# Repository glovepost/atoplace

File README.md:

<p align="center">
  
</p>

---

<p align="center">
  <strong>The AI Pair Designer for Professional PCB Layout</strong>
</p>

**atoplace** is an intelligent orchestration layer for PCB design that bridges the gap between schematic and physical layout. It automates the tedious 80% of design—placement optimization and DFM validation—while strictly adhering to "Manhattan" aesthetics and Signal Integrity (SI) best practices.

Designed to work seamlessly with **[atopile](https://atopile.io)** and **[KiCad](https://kicad.org)**.

## 🚀 Why atoplace?

PCB layout automation has historically been "black box" and "messy"—producing organic, unreadable layouts that professional engineers reject. atoplace takes a different approach:

*   **Human-Grade Aesthetics**: We don't just minimize wirelength. We enforce **grids**, **alignment**, and **orthogonal routing** so the result looks like *you* designed it.
*   **Physics-First**: We model high-degree nets (GND/VCC) correctly to prevent component collapse, and prioritize critical signals (USB, RF) before general routing.
*   **Transparent & Interactive**: No lock-in. The source of truth is always your `.kicad_pcb` file. You can take over manually at any second.

## ✨ Key Features

- **🧩 Manhattan Legalizer**: Transforms "organic" force-directed placements into professional, grid-snapped, and row-aligned layouts using PCA axis detection and Abacus-style overlap resolution.
- **🧠 Intelligent Placement**: Force-directed annealing engine with a **Star Model** for stable high-degree net (GND/VCC) handling and adaptive damping for oscillation control.
- **🚀 A* Routing**: High-performance, deterministic geometric router using a **Greedy Multiplier** ($w=2-3$) and **Spatial Hash Indexing** for O(~1) collision detection.
- **🔍 Confidence Scoring**: Automated assessment of your board's routability, signal integrity risks, and DFM compliance.
- **💬 Natural Language Control**: "Move the USB connector to the left edge", "Align these capacitors", "Keep the crystal near the MCU".
- **🔌 Atopile Native**: First-class support for `atopile` projects with `ato-lock.yaml` parsing, module-aware grouping, and **`atoplace.lock` sidecar persistence** to preserve placements across rebuilds.
- **📊 Interactive Visualization**: Unified SVG delta viewer with real-time playback, layer toggles, grid customization, force vector display, routing trace visualization, and A* debug mode for step-by-step algorithm analysis.

## 🛠️ Installation

```bash
pip install atoplace
```

### Requirements
- **Python 3.10+**
- **KiCad 8.0+** (atoplace uses the `pcbnew` Python API)

> **Pro Tip:** atoplace works best when run using the Python interpreter bundled with KiCad:

**macOS:**
```bash
/Applications/KiCad/KiCad.app/Contents/Frameworks/Python.framework/Versions/Current/bin/python3 -m pip install atoplace
```

**Windows:**
```powershell
"C:\Program Files\KiCad\8.0\bin\python.exe" -m pip install atoplace
```

## ⚡ Quick Start

### 1. Optimize Placement
Automatically place components with "Manhattan" legalization:
```bash
atoplace place board.kicad_pcb --grid 0.5 --constraints "USB on left edge"
```

### 2. Route the Board
Route all nets using the internal A* geometric planner:
```bash
atoplace route board.kicad_pcb --visualize
```

### 3. Validate Layout
Check your board against DFM rules (JLCPCB, OSH Park, etc.):
```bash
atoplace validate board.kicad_pcb --dfm jlcpcb_standard
```

### 4. Interactive Mode
Refine your design using natural language:
```bash
atoplace interactive board.kicad_pcb
# > "Rotate U1 45 degrees"
# > "Move C1 closer to U1"
# > "Save"
```

### 5. MCP Server (LLM Integration)
Expose atoplace tools to AI agents via the Model Context Protocol:
```bash
atoplace mcp --launch
```

See [MCP Server](#-mcp-server) section below for details.

## 🗺️ Roadmap

- **Milestone A (Q1 2026): Solid Foundation** ✅
  - [x] Manhattan Legalizer (Grid snapping & PCA Alignment).
  - [x] Physics Engine scaling (Star Model & Adaptive Damping).
  - [x] Atopile `ato-lock.yaml` and module hierarchy integration.
- **Milestone B (Q1-Q2 2026): Routing & Persistence** ✅
  - [x] **A* Geometric Planner** (Greedy Multiplier & Spatial Indexing).
  - [x] **MCP Server** with 40+ tools for LLM agent integration.
  - [x] **Live KiCad IPC** via kipy for real-time component manipulation (KiCad 9+).
  - [x] **`atoplace.lock` Sidecar Persistence** for atopile projects.
  - [x] **Unified Visualization** (SVG delta viewer with routing support).
  - [x] **BGA/QFN Fanout Generator** (dogbone & via-in-pad strategies).
  - [x] **Pin Swap Optimization** (bipartite matching for crossing reduction).
- **Milestone C (Q2 2026): Professional Agent** 🚧
  - [x] Differential Pair Detection (auto-detect from net names).
  - [ ] Differential Pair Coupled Routing.
  - [ ] Deep Signal Integrity Analysis (Crosstalk/Impedance).
  - [ ] Automated Manufacturing Outputs (Gerbers/BOM/PNP).
  - [ ] Multi-board design support.

## 📂 Architecture

```
atoplace/
├── board/          # Board abstraction & KiCad/Atopile adapters
│   ├── abstraction.py      # Board, Component, Net, Pad data models
│   ├── kicad_adapter.py    # KiCad pcbnew integration
│   ├── lock_file.py        # atoplace.lock sidecar persistence
│   └── atopile_adapter.py  # Atopile project loader
├── placement/      # Force-directed physics & Manhattan Legalizer
│   ├── force_directed.py   # Physics Engine (Star Model, adaptive damping)
│   ├── legalizer.py        # Manhattan Pipeline with PCA alignment
│   ├── module_detector.py  # Functional module hierarchy analysis
│   ├── constraints.py      # Placement constraints (Proximity, Edge, Zone, etc.)
│   └── visualizer.py       # SVG delta visualization with frame capture
├── routing/        # A* Geometric Router
│   ├── astar_router.py     # Core A* with Greedy Multiplier (w=2-3)
│   ├── manager.py          # Multi-phase routing pipeline
│   ├── spatial_index.py    # O(~1) collision detection via spatial hashing
│   ├── obstacle_map.py     # Obstacle generation from board
│   ├── diff_pairs.py       # Differential pair detection
│   ├── visualizer.py       # Routing visualization with A* debug
│   └── fanout/             # BGA/QFN escape routing
├── visualization/  # Unified visualization system
│   └── assets/             # External JS/CSS for HTML viewer
│       ├── svg-delta-viewer.js  # Interactive SVG playback engine
│       └── styles.css      # KiCad-inspired dark theme
├── nlp/            # Natural Language & Intent Engine
│   └── constraint_parser.py  # Parse "USB on left edge" to constraints
├── validation/     # Confidence Scorer & DFM/DRC Checker
│   ├── confidence.py       # Design quality assessment
│   └── drc.py              # Design rule checking
├── mcp/            # MCP Server for LLM Integration
│   ├── server.py           # FastMCP server with 40+ tools
│   ├── backends.py         # Backend mode detection & factory
│   ├── kipy_session.py     # Live KiCad IPC session (KiCad 9+)
│   └── context/            # Context generators (semantic grid, module map)
└── cli.py          # CLI entry point
```

## 🤖 MCP Server

atoplace includes a **Model Context Protocol (MCP)** server that exposes 40+ PCB design tools to LLM agents like Claude. This enables conversational PCB layout design with support for placement, routing, fanout generation, and design validation.

### Quick Start

Just run:
```bash
python -m atoplace.mcp.launcher
```

That's it! The launcher:
- **Auto-detects** KiCad Python on macOS, Linux, and Windows
- **Starts** the KiCad bridge (for pcbnew access)
- **Starts** the MCP server (exposes tools to LLM)
- **Manages** lifecycle and clean shutdown

### Claude Code / Claude Desktop Configuration

Add to your MCP config:

```json
{
  "mcpServers": {
    "atoplace": {
      "command": "python",
      "args": ["-m", "atoplace.mcp.launcher"]
    }
  }
}
```

> **Note**: Replace `python` with the path to your atoplace virtualenv Python if needed.

### 🔴 Live KiCad IPC Mode (KiCad 9+)

**New!** With KiCad 9+, atoplace can manipulate components in real-time without save/reload cycles. Changes appear instantly in your KiCad viewport!

**Requirements:**
- KiCad 9.0 or later (with IPC API enabled)
- `kicad-python` package: `pip install kicad-python`

**Setup:**
```bash
# Install the kipy optional dependency
pip install atoplace[kipy]

# Or install directly
pip install kicad-python
```

**Usage:**
1. Open your `.kicad_pcb` in KiCad 9+ PCB Editor
2. Start the MCP server with the kipy backend:
   ```bash
   ATOPLACE_BACKEND=kipy python -m atoplace.mcp.launcher
   ```
3. Components move instantly as you interact with the LLM!

**How it works:** The kipy backend connects directly to KiCad's IPC socket and uses the official API to update component positions in real-time. Native undo/redo (Cmd/Ctrl+Z) works seamlessly.

### Architecture

```mermaid
flowchart LR
    subgraph MCP["MCP Server (Python 3.10+)"]
        direction TB
        FastMCP[FastMCP]
        Tools[26 Layout Tools]
        Context[Context Generators]
    end

    subgraph KiPy["KiPy Backend (KiCad 9+)"]
        direction TB
        IPC[KiCad IPC API]
        LiveEdit[Real-time Updates]
        NativeUndo[Native Undo/Redo]
    end

    subgraph Bridge["KiCad Bridge (KiCad 8.x)"]
        direction TB
        pcbnew[pcbnew API]
        BoardIO[Board I/O]
        UndoRedo[Undo/Redo]
    end

    MCP <-->|"KiCad IPC\nSocket"| KiPy
    MCP <-->|"Unix Socket\nJSON-RPC"| Bridge
```

**Backend Modes:**
| Mode | KiCad Version | Real-time | How it works | Status |
|------|--------------|-----------|--------------|--------|
| `kipy` | 9.0+ | ✅ Yes | Direct IPC API connection | **Default** |
| `ipc` | 8.0+ | ❌ No | File-based bridge process | Fallback |
| `direct` | 8.0+ | ❌ No | Direct file manipulation | Fallback |

**Note:** KIPY mode is the primary backend for bleeding-edge development. It provides instant visual feedback in KiCad's viewport and native undo/redo integration. The server automatically falls back to IPC or direct mode if KIPY is unavailable.

### Available Tools (40+ total)

| Category | Tools |
|----------|-------|
| **Board Management** | `load_board`, `save_board`, `undo`, `redo` |
| **Placement Actions** | `move_absolute`, `move_relative`, `rotate`, `place_next_to`, `align_components`, `distribute_evenly`, `stack_components`, `arrange_pattern`, `cluster_around`, `lock_components` |
| **Discovery** | `find_components`, `get_board_summary`, `get_unplaced_components` |
| **Routing** | `route_board`, `route_net`, `detect_diff_pairs`, `get_routing_preview`, `analyze_pin_swaps`, `optimize_pin_swaps`, `export_pin_constraints` |
| **BGA/Fanout** | `detect_bga_components`, `fanout_component`, `fanout_all_bgas`, `get_fanout_preview` |
| **Context** | `inspect_region`, `get_semantic_grid`, `get_module_map` |
| **Validation** | `check_overlaps`, `validate_placement`, `run_drc`, `get_crossing_analysis` |
| **Optimization** | `optimize_placement`, `detect_modules`, `parse_constraint`, `get_atopile_context` |

### Environment Variables (Optional)

| Variable | Description | Default |
|----------|-------------|---------|
| `ATOPLACE_BACKEND` | Backend mode: `kipy`, `ipc`, or `direct` | `kipy` (with fallback) |
| `ATOPLACE_USE_KIPY` | Enable kipy mode (`1` or `true`) | Deprecated - use `ATOPLACE_BACKEND` |
| `KICAD_PYTHON` | Override KiCad Python path | Auto-detected |
| `ATOPLACE_LOG` | Log file location | `/tmp/atoplace.log` |

**Default behavior:** The server attempts KIPY first, then falls back to IPC, then direct mode. For bleeding-edge KiCad 9+ users, no configuration is needed - KIPY mode activates automatically when KiCad is running with IPC enabled.

### Example LLM Conversation

```
User: Load the board at examples/dogtracker/layouts/default/default.kicad_pcb

Claude: [Calls load_board tool]
Board loaded successfully:
- 37 components
- 72 nets

User: Find all the capacitors and align them horizontally

Claude: [Calls find_components with query="C", filter_by="ref"]
Found 12 capacitors: C1, C2, C3...

[Calls align_components with refs=["C1","C2",...], axis="y"]
Aligned 12 capacitors along the Y axis.

User: Check if there are any overlaps

Claude: [Calls check_overlaps]
No overlapping components detected. The placement is valid.

User: Save the board

Claude: [Calls save_board]
Board saved to: examples/dogtracker/layouts/default/default.placed.kicad_pcb
```

## 🔒 Atopile Lock File Persistence

When working with **atopile** projects, placement positions can be lost when `ato build` regenerates the KiCad board. The `atoplace.lock` sidecar file solves this by persisting component positions between builds.

### How it works

After placement, atoplace automatically saves positions to a lock file next to the board:
```
my-project/
├── elec/
│   └── layout/
│       └── default/
│           ├── default.kicad_pcb
│           └── default.atoplace.lock  ← Saved positions
└── ato.yaml
```

### Lock File Format

```yaml
version: 1
created: 2026-01-14T10:30:00
build: default
components:
  U1:
    x: 125.5
    y: 80.0
    rotation: 0.0
    locked: true    # User-approved position
    module: mcu
  C1:
    x: 130.0
    y: 85.5
    locked: false   # Auto-placed, can be re-optimized
```

### CLI Options

| Flag | Description |
|------|-------------|
| `--use-lock` | Apply saved positions before placement |
| `--only-locked` | Only restore `locked: true` positions |
| `--save-lock/--no-save-lock` | Auto-save after placement (default: on) |
| `--lock-all` | Mark all positions as user-approved |

### Workflow Example

```bash
# First placement - automatically saves lock file
atoplace place my-project/ --use-ato-modules

# After `ato build` regenerates board - restore positions
atoplace place my-project/ --use-lock

# Only restore approved positions, re-optimize others
atoplace place my-project/ --use-lock --only-locked

# Approve all current positions
atoplace place my-project/ --lock-all
```

### Merge Logic

The lock file uses **Lock > Physics** priority:
1. `locked: true` positions always preserved (user-approved)
2. `locked: false` positions used as initial hints, can be re-optimized
3. New components (not in lock file) placed by physics engine

## 📄 License

MIT License - see [LICENSE](LICENSE) for details.

## 🙏 Acknowledgments

*   **[atopile](https://github.com/atopile/atopile)**: The declarative language that makes code-driven hardware possible.
*   **[KiCad](https://kicad.org)**: The open-source EDA standard we build upon.
*   **[kicad-python](https://github.com/kicad/kicad-python)**: Official Python bindings for KiCad's IPC API.
*   **[Freerouting](https://github.com/freerouting/freerouting)**: The open-source autorouting engine.

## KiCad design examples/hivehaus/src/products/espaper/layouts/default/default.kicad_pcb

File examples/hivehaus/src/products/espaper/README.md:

# espaper

ESPHome waveshare epaper driver

Created by Nicholas Krstevski <nick@atopile.io>

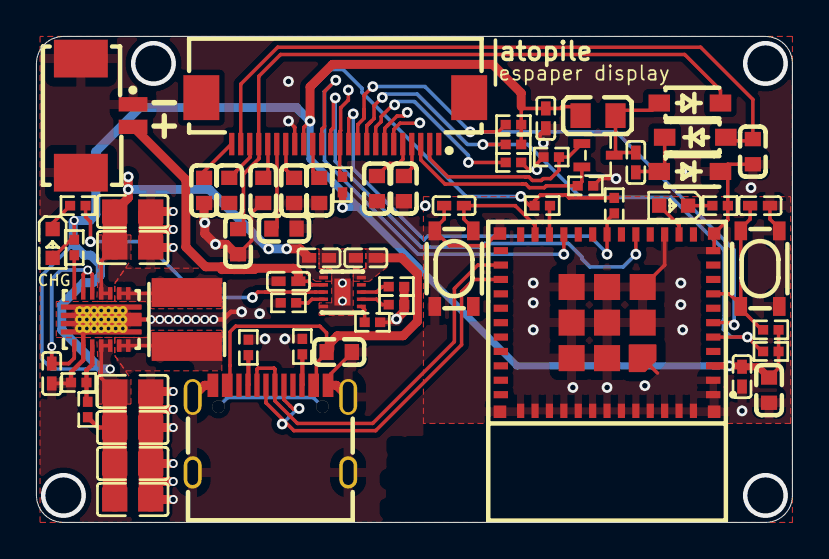
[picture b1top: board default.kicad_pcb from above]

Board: 2 copper layers, 42.0 x 27.0 mm, 66 parts (1 on the bottom side), 46 nets.

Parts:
B1: EEMB_BATTERY_LP402535
C1: 4.7µF ±20% 10V X5R; C0402
C2, C5, C6, C7, C8, C9, C10, C11, C12, C13: 1µF ±10% 50V X5R; C0603
C3, C4: 10µF ±10% 25V X5R; C0805
C14, C15, C17, C24: 100nF ±10% 16V X7R; C0402
C16: 22µF ±20% 6.3V X5R; C0603
C18, C25, C27: 1µF ±10% 25V X5R; C0402
C19: 4.7µF ±10% 16V X5R; C0603
C20, C21, C22, C23: 22µF ±20% 6.3V X5R; C0805
C26: 10µF ±20% 6.3V X5R; C0402
D1, D2, D3: SOD-123_L2.7-W1.6-LS3.7-RD-1
FPC1: FPC-SMD_24P-P0.50_FPC-05F-24PH20
L1: 1µH ±20% 4.7A 18mΩ; IND-SMD_L4.0-W4.0_FNR40XXS
L2: 68µH ±20% 50mA 6Ω; L0805
LED1, LED2: LED0603-RD
LOGO1: atopile_Logo_4x4mm
Q1: SOT-323-3_L2.0-W1.3-P1.30-LS2.1-BR
R1: 200kΩ ±1% 62.5mW; R0402
R2: 1.2MΩ ±1% 62.5mW; R0402
R3: 3.3Ω ±1% 62.5mW; R0402
R4, R6, R7, R8, R9, R11, R12, R16, R18, R19, R20, R21: 10kΩ ±1% 62.5mW; R0402
R5: 1MΩ ±1% 62.5mW; R0402
R10: 470mΩ ±1%; R0402
R13, R14: 4.7kΩ ±1% 62.5mW; R0402
R15: 2kΩ ±1% 62.5mW; R0402
R17: 18kΩ ±1% 62.5mW; R0402
SW1, SW2: KEY-SMD_4P-L4.2-W3.2-P2.20-LS4.6
U1: CONN-SMD_532610271
U2: WIFIM-SMD_ESP32-C3-MINI-1
U3: VSON-14_L4.0-W3.0-P0.50-BL-EP_TI_DSJ
U4: WSON-10_L2.2-W2.0-P0.40-BL-EP_TI_DLH0010A
USB1: USB-C-SMD_KH-TYPE-C-16P

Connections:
A5: R13.1, USB1.A5
B5: R14.1, USB1.B5
EPD_BUSY: FPC1.9, R4.1, R7.1, U2.5
EPD_DC: FPC1.11, R6.1, U2.18
EPD_RST: FPC1.10, R12.1, U2.6
EPD_SPI_CS: FPC1.12, R18.1
EPD_SPI_MISO: R8.1, U2.22
EPD_SPI_MOSI: FPC1.14, U2.21
EPD_SPI_SCLK: FPC1.13, U2.16
ILIM_VSET: R17.1, U4.7
ISET: R15.1, U4.8
L1: L1.1, U3.8, U3.9
L2: L1.2, U3.6, U3.7
N_TRST: C15.2, R9.2, SW2.3, SW2.4, U2.8
PG: R5.1, U3.14
POWER_3V3: C1.1, C16.1, C17.1, C20.1, C21.1, C22.1, C23.1, FPC1.16, L2.1, LED2.2, R2.1, R4.2, R5.2, R6.2, R7.2, R8.2, R9.1, R12.2, R18.2, U2.3, U3.4, U3.5
POWER_VBUS: C19.1, C27.1, U4.10, USB1.A4, USB1.A9, USB1.B4, USB1.B9
TS_MR: R19.1, U4.6
USB_D_N: U2.26, USB1.A7, USB1.B7
USB_D_P: U2.27, USB1.A6, USB1.B6
VDIV_OUTPUT: R1.1, R2.2, U3.3
_power_in_a-VCC: C24.1, U3.1, U3.12, U3.13
blue_led-cathode: LED1.1, R20.1
bs-line: FPC1.8, R3.1
charge_pump_inductor-anode: C18.2, D2.2, L2.2, Q1.3
d_gnd-anode: C18.1, D1.2, D3.1
footprint-cathode: LED2.1, R21.1
gate: FPC1.2, Q1.1, R11.1
model-power-GND: C1.2, C2.2, C3.2, C4.2, C5.2, C6.2, C7.2, C8.2, C9.2, C10.2, C11.2, C12.2, C13.2, C14.1, C15.1, C16.2, C17.2, C19.2, C20.2, C21.2, C22.2, C23.2, C24.2, C25.2, C26.2, C27.2, D1.1, FPC1.17, R1.2, R3.2, R10.2, R11.2, R13.2, R14.2, R15.2, R16.2, R17.2, R19.2, R20.2, SW1.1, SW1.2, SW2.1, SW2.2, U1.1, U1.3, U1.4, U2.1, U2.2, U2.11, U2.14, U2.36, U2.37, U2.38, U2.39, U2.40, U2.41, U2.42, U2.43, U2.44, U2.45, U2.46, U2.47, U2.48, U2.49, U2.50, U2.51, U2.52, U2.53, U3.2, U3.15, U4.5, U4.11, USB1.1, USB1.2, USB1.3, USB1.4, USB1.A1, USB1.A12, USB1.B1, USB1.B12
nCE: R16.1, U4.4
output: C14.2, SW1.3, SW1.4, U2.23
power-VCC: C25.1, U1.2, U4.2
power-anode: LED1.2, U2.13
power_sys-VCC: C3.1, C4.1, C26.1, U3.10, U3.11, U4.1
prevgh-cathode: C10.1, D2.1, FPC1.21
prevgl-anode: C12.1, D3.2, FPC1.23
red_led-power-GND: R21.2, U4.3
source: FPC1.3, Q1.2, R10.1
vcom-line: C13.1, FPC1.24
vdd-line: C7.1, FPC1.18
vddio: C2.1, FPC1.15
vgh-line: C6.1, FPC1.5
vgl-line: C5.1, FPC1.4
vpp-line: C8.1, FPC1.19
vsh-line: C9.1, FPC1.20
vsl-line: C11.1, FPC1.22

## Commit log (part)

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2026-01-12 Add PNG logo banner
2026-01-15 Reorganize test scripts: move root tests to scripts/ directory
    - Move test_*.py and create_test_components.py from root to scripts/
    - Update pyproject.toml to include scripts/ in pytest testpaths
    - Fix AttributeError in scripts/test_canvas_export.py (MockComponent missing layer)
    - Wrap test_canvas_export.py execution in main() block
2026-01-15 Docs: Add ISSUES.md tracking technical debt and feature gaps
2026-01-16 Core: fix IPC/KiPy sync and routing fanout
2026-01-19 Fix pad-aware overlap handling
